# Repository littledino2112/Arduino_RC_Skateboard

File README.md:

This project is created to provide schematics, PCB layout as well as Arduino sketches for both transmitter and receiver used in controlling Electric Skateboard.
CAUTION: Used at your own risk.

How to wire up nRF24 breakout board to Arduino Uno:
nRF24 ----- Uno
  1   ----- GND
  2   ----- VCC
  3   -----  7 (Chip enable)
  4   -----  8 (SPI Chip select)
  5   -----  13 (SPI Clock)
  6   -----  11 (SPI MOSI)
  7   -----  12 (SPI MISO)

Hoang Nguyen

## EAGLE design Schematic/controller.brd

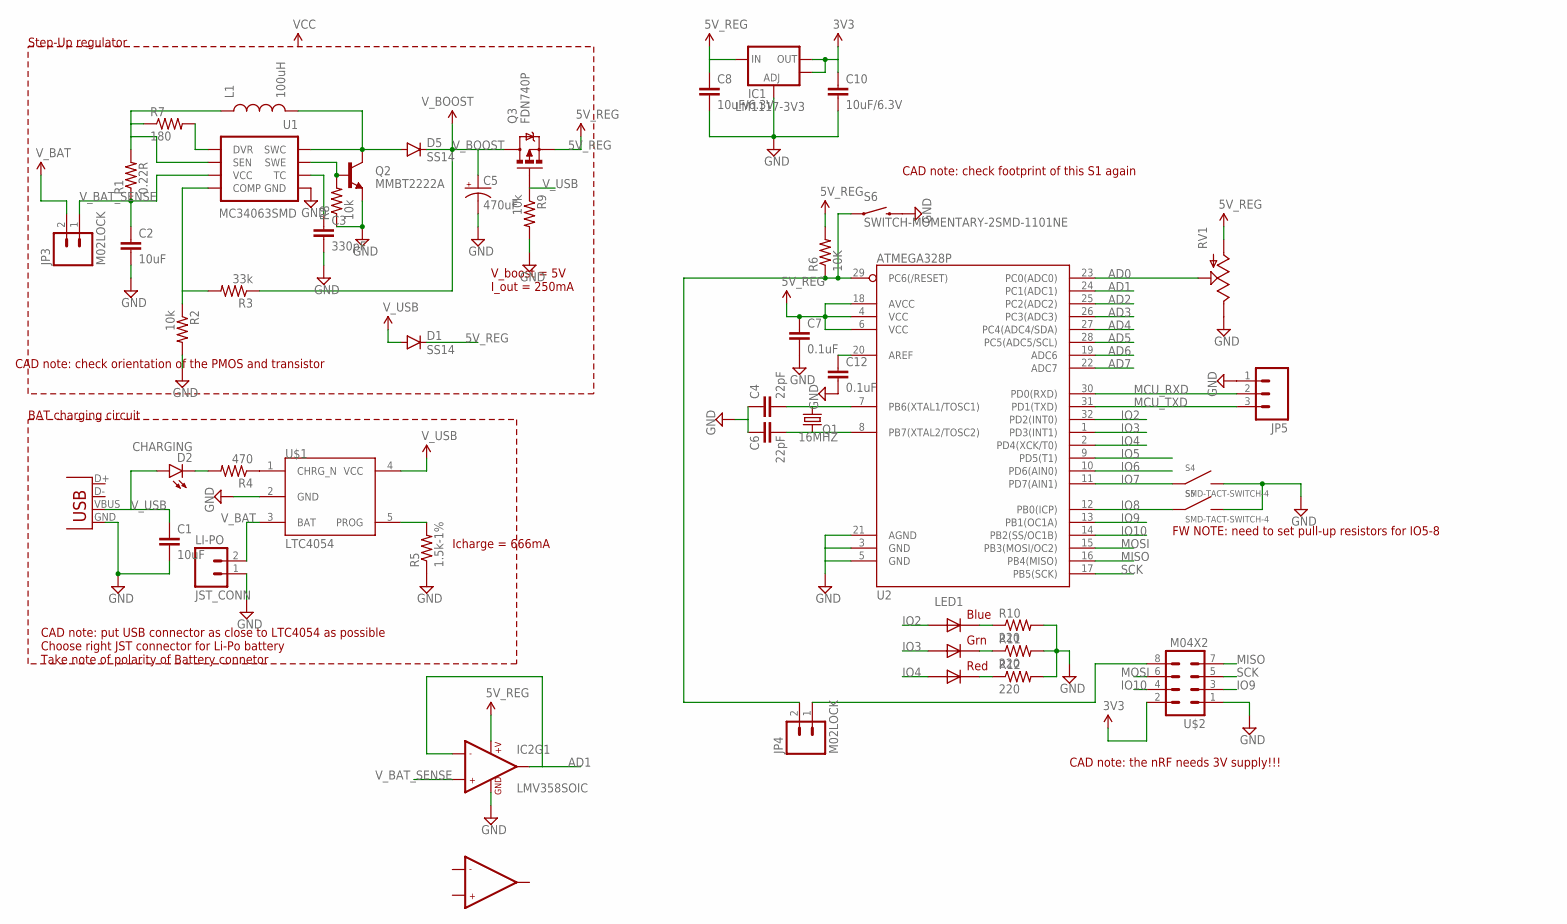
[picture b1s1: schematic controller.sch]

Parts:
C1, C2: 10uF; 0603-CAP
C3: 330pF; 0805
C4, C6: 22pF; 0603-CAP
C5: 470uF; EIA7343
C7, C12: 0.1uF; 0603-CAP
C8, C10: 10uF/6.3V; 0603-CAP
D1, D5: SS14; SMA-DIODE_ALT
D2: CHARGING; LED-0603
IC1: LM1117-3V3; SOT223
IC2: LMV358SOIC; SO08
JP1: USB-SMD-NS; USB-MINIB-NOSTOP
JP3, JP4: M02LOCK; 1X02_LOCK
JP5: M03LOCK; 1X03_LOCK
L1: 100uH; SRN6045
LED1: RGBLED5050
LI-PO: JST_CONN; JST-2-PTH-VERT
Q1: 16MHZ; HC49/S
Q2: MMBT2222A; SOT23-3
Q3: FDN740P; SOT23-3
R1: 0.22R; 0805
R2, R8, R9: 10k; 0603-RES
R3: 33k; 0603-RES
R4: 470; 0603-RES
R5: 1.5k-1%; 0805
R6: 10K; 0603-RES
R7: 180; 0603-RES
R10, R11, R12: 220; 0603-RES
RV1: POT-RV16AF-20; POT_ALPHA_RV16AF-20
S4, S5: SMD-TACT-SWITCH-4; SMD-TACTSWITCH-6X6X3
S6: SWITCH-MOMENTARY-2SMD-1101NE; TACTILE-SWITCH-1101NE
U1: MC34063SMD; SO08
U2: ATMEGA328P; TQFP32-08
U$1: LTC4054; SOT23-5
U$2: M04X2; 2X4

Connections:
3V3: C10.1, IC1.2 (OUT), IC1.4 (OUT), U$2.2
5V_REG: C7.1, C8.1, D1.C, IC1.3 (IN), IC2.8 (+V), Q3.2 (S), R6.2, RV1.1 (A), U2.4 (VCC), U2.6 (VCC), U2.18 (AVCC)
AD0: RV1.2 (S), U2.23 (PC0(ADC0))
AD1: IC2.1 (OUT1), IC2.2 (-IN1), U2.24 (PC1(ADC1))
AD2: U2.25 (PC2(ADC2))
AD3: U2.26 (PC3(ADC3))
AD4: U2.27 (PC4(ADC4/SDA))
AD5: U2.28 (PC5(ADC5/SCL))
AD6: U2.19 (ADC6)
AD7: U2.22 (ADC7)
GND: C1.2, C2.2, C3.2, C4.1, C5.C (-), C6.1, C7.2, C8.2, C10.2, C12.2, IC1.1 (ADJ), IC2.4 (GND), JP1.GND, JP5.1, LI-PO.1, Q2.2 (E), R2.2, R5.1, R8.1, R9.2, R10.2, R11.2, R12.2, RV1.3 (E), S4.P$2, S5.P$2, S6.2, U1.4 (GND), U2.3 (GND), U2.5 (GND), U2.21 (AGND), U$1.2 (GND), U$2.1
IO2: LED1.3 (BLUE_A), U2.32 (PD2(INT0))
IO3: LED1.1 (GREEN_A), U2.1 (PD3(INT1))
IO4: LED1.2 (RED_A), U2.2 (PD4(XCK/T0))
IO5: U2.9 (PD5(T1))
IO6: U2.10 (PD6(AIN0))
IO7: S4.P$1, U2.11 (PD7(AIN1))
IO8: S5.P$1, U2.12 (PB0(ICP))
IO9: U2.13 (PB1(OC1A)), U$2.3
IO10: U2.14 (PB2(SS/OC1B)), U$2.4
MCU_RXD: JP5.2, U2.30 (PD0(RXD))
MCU_TXD: JP5.3, U2.31 (PD1(TXD))
MISO: U2.16 (PB4(MISO)), U$2.7
MOSI: U2.15 (PB3(MOSI/OC2)), U$2.6
unnamed: C4.2, Q1.2, U2.7 (PB6(XTAL1/TOSC1))
unnamed: R5.2, U$1.5 (PROG)
unnamed: Q2.1 (B), R8.2, U1.2 (SWE)
unnamed: R2.1, R3.2, U1.5 (COMP)
unnamed: C6.2, Q1.1, U2.8 (PB7(XTAL2/TOSC2))
unnamed: JP4.2, R6.1, S6.1, U2.29 (PC6(/RESET))
unnamed: D2.C, R4.2
unnamed: R4.1, U$1.1 (CHRG_N)
unnamed: R7.2, U1.8 (DVR)
unnamed: C3.1, U1.3 (TC)
unnamed: LED1.4 (BLUE_C), R10.1
unnamed: C12.1, U2.20 (AREF)
unnamed: LED1.6 (GREEN_C), R11.1
unnamed: LED1.5 (RED_C), R12.1
unnamed: JP4.1, U$2.8
PWR_L1: L1.1, R1.2, R7.1, U1.7 (SEN)
PWR_L2: D5.A, L1.2, Q2.3 (C), U1.1 (SWC)
SCK: U2.17 (PB5(SCK)), U$2.5
V_BAT: JP3.2, LI-PO.2, U$1.3 (BAT)
V_BAT_SENSE: C2.1, IC2.3 (+IN1), JP3.1, R1.1, U1.6 (VCC)
V_BOOST: C5.A (+), D5.C, Q3.3 (D), R3.1
V_USB: C1.1, D1.A, D2.A, JP1.VBUS, Q3.1 (G), R9.1, U$1.4 (VCC)

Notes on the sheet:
CAD note: check orientation of the PMOS and transistor
CAD note: put USB connector as close to LTC4054 as possible Choose right JST connector for Li-Po battery Take note of polarity of Battery connetor
Step-Up regulator
BAT charging circuit
V_boost = 5V I_out = 250mA
Icharge = 666mA
CAD note: the nRF needs 3V supply!!!
CAD note: check footprint of this S1 again
FW NOTE: need to set pull-up resistors for IO5-8

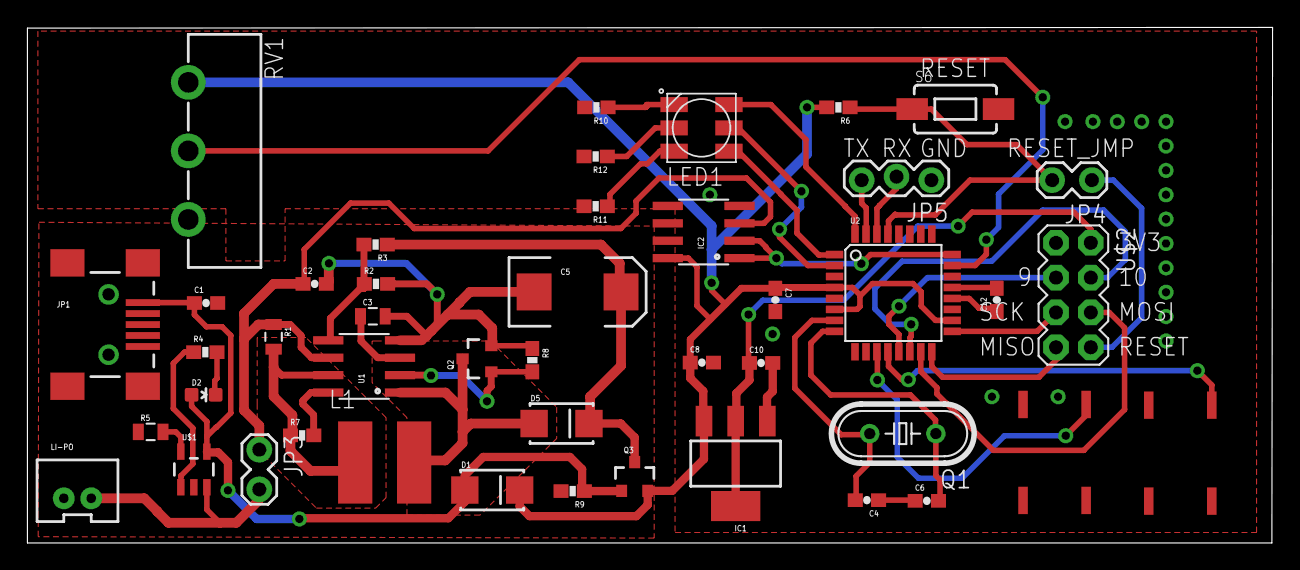
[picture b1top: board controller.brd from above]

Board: 2 copper layers, 90.8 x 37.6 mm, 45 parts (0 on the bottom side), 38 nets.

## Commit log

2014-12-09 Initial commit. Working prototype to transmit 1 byte from transmitter to receiver
2014-12-09 Include header files into each folder
2014-12-09 Transmitter can control an LED indicator from a receiver now./joystick_gui.app/ Add tag v0.1
2014-12-09 Add instruction on how to wire the nRF24 to Arduino Uno
2014-12-15 Add initial schematic for controller
2014-12-15 First completed draft schematic for the controller
2014-12-16 Add initial PCB layout of the controller
2014-12-16 Completed layout for the controller

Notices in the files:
parts and their libraries:
SparkFun-Capacitors: Licensing: Creative Commons ShareAlike 4.0 International - https://creativecommons.org/licenses/by-sa/4.0
